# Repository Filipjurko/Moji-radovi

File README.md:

# Moji-radovi
Neki od mojih dosadašnjih radova.
Rađeni su iz razonode i zbog želje za učenjem programiranja u Arduino i C++ environmentu,
te cratnja u ad programima kao što su Fusion 360 i Solidworks.
Nekoliko od ovih projekata išlo je na natjecanja i svi su dobivali nagrade. 
Trenutno nemam ni jedan fizički izrađen projekt jer sam sve prototipe prodao ili ih poklonio.
KOntaktiram vas iz želje za učenjem ranog dizajna proizvoda i kako ga izbaciti na tržište kroz suradnju
s vašom kompanijom. Nadam se da ćete uvažiti moj upit. Hvala.

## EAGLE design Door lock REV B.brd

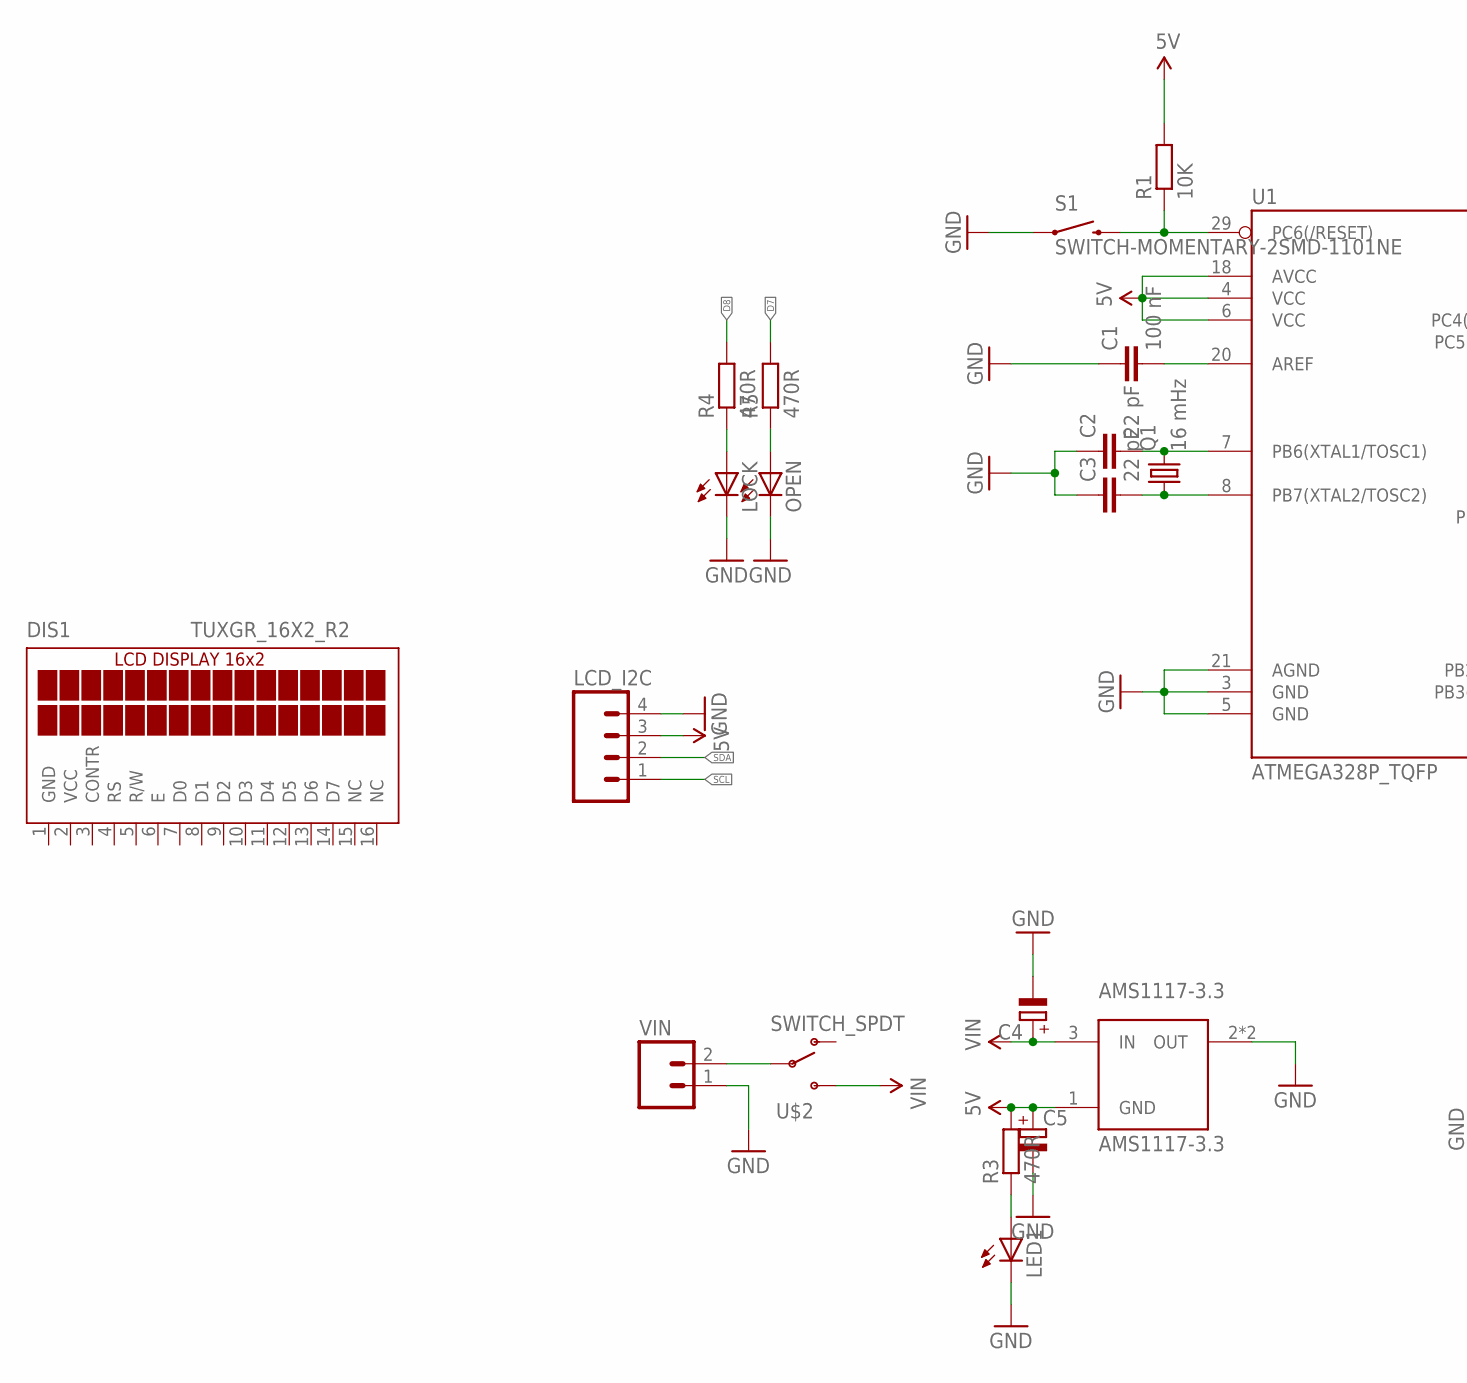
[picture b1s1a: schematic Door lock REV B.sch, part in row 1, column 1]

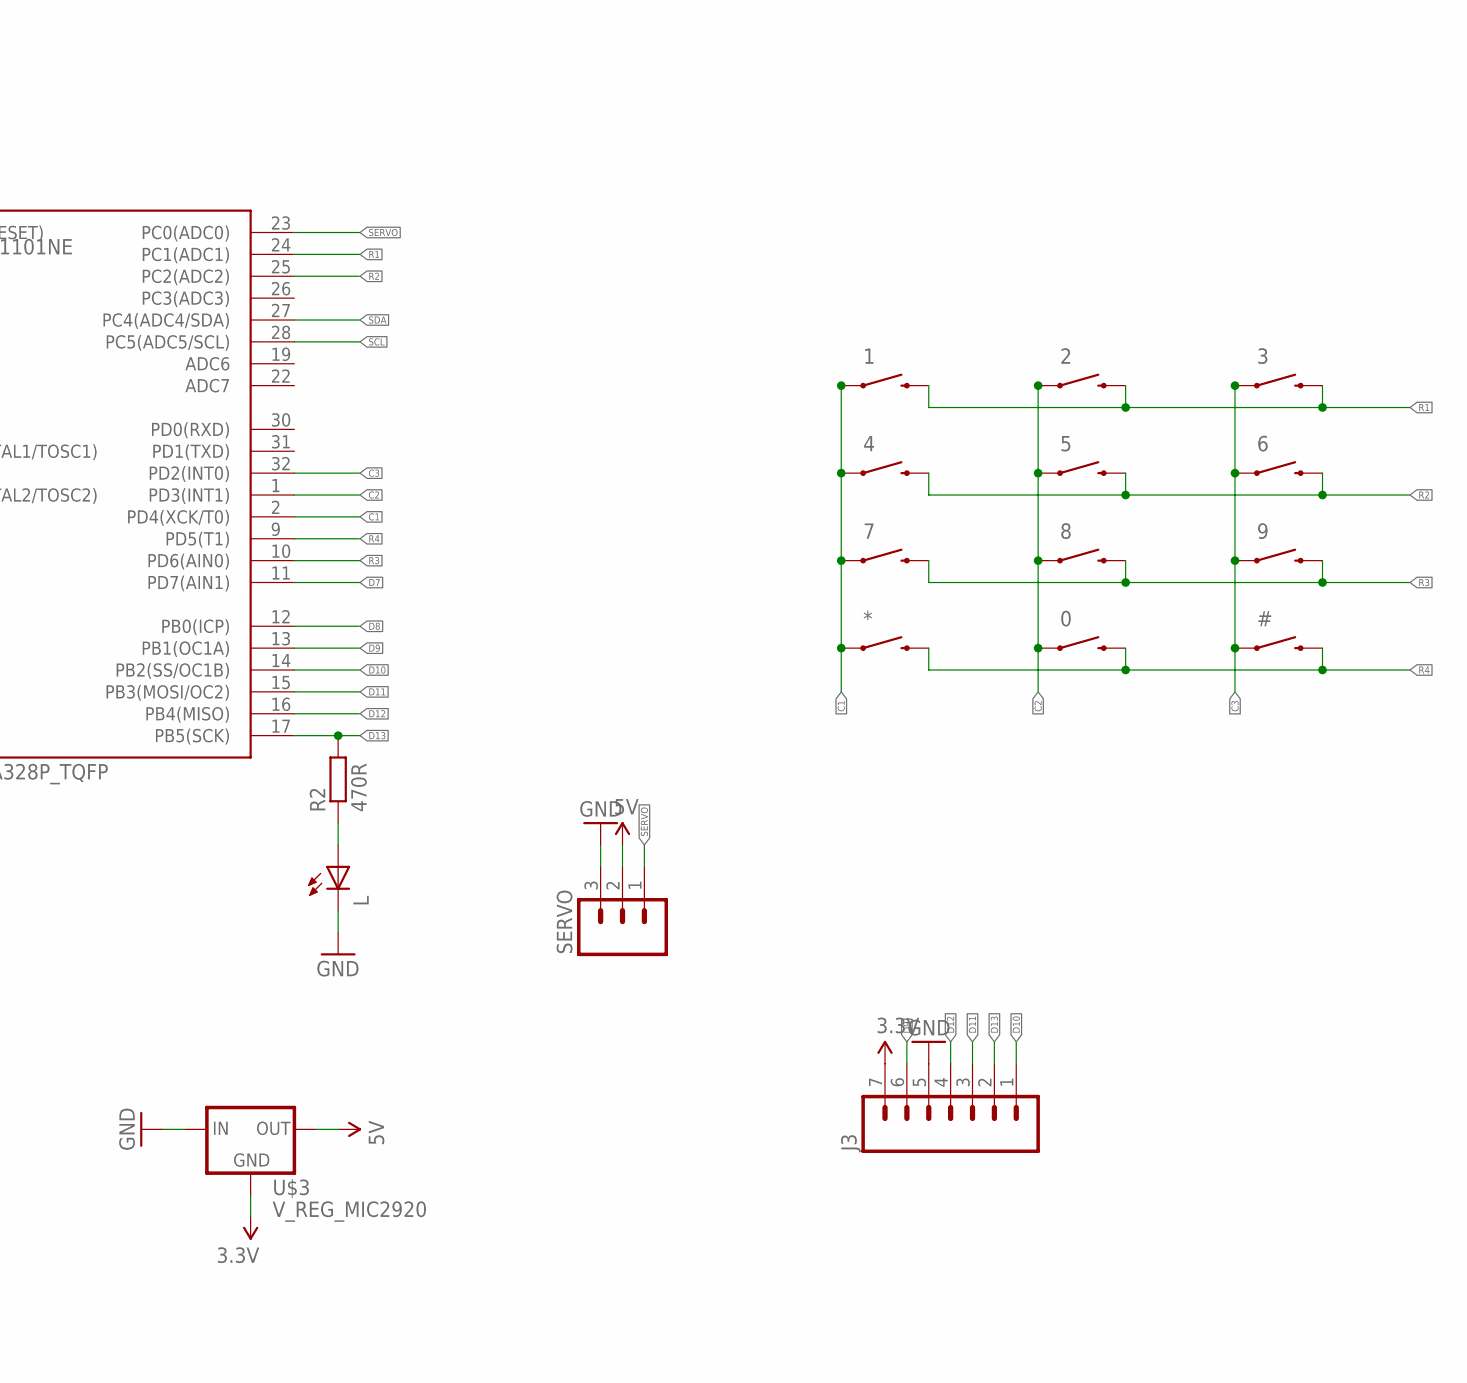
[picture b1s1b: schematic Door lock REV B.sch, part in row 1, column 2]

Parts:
0, 1, 2, 3, 4, 5, 6, 7, 8, 9: SWITCH-MOMENTARY-2PTH; TACTILE-PTH
#: SWITCH-MOMENTARY-2PTH; TACTILE-PTH
*: SWITCH-MOMENTARY-2PTH; TACTILE-PTH
AMS1117-3.3: AMS1117-3.3; SOT89
C1: 100 nF; C0603
C2, C3: 22 pF; C0603
C4, C5: CPOL-EUSMCA; SMC_A
DIS1: TUXGR_16X2_R2
J3: M07; 1X07
L: LEDCHIPLED_0805; CHIPLED_0805
LCD_I2C: M04PTH; 1X04
LED1: LEDCHIPLED_0805; CHIPLED_0805
LOCK: LED3MM
OPEN: LED3MM
Q1: 16 mHz; HC49/S
R1: 10K; R0603
R2, R3, R4, R5: 470R; R0603
S1: SWITCH-MOMENTARY-2SMD-1101NE; TACTILE-SWITCH-1101NE
SERVO: M03PTH; 1X03
U1: ATMEGA328P_TQFP; TQFP32-08
U$2: SWITCH_SPDT; KPS-1290
U$3: V_REG_MIC2920; SOT223
VIN: M02PTH3; 1X02_LONGPADS

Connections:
3.3V: J3.7, U$3.2 (GND)
5V: AMS1117-3.3.1 (GND), C5.+, LCD_I2C.3, R1.2, R3.2, SERVO.2, U1.4 (VCC), U1.6 (VCC), U1.18 (AVCC), U$3.3 (OUT)
C1: 1.1, 4.1, 7.1, *.1, U1.2 (PD4(XCK/T0))
C2: 0.1, 2.1, 5.1, 8.1, U1.1 (PD3(INT1))
C3: 3.1, 6.1, 9.1, #.1, U1.32 (PD2(INT0))
D7: R5.2, U1.11 (PD7(AIN1))
D8: R4.2, U1.12 (PB0(ICP))
D9: J3.6, U1.13 (PB1(OC1A))
D10: J3.1, U1.14 (PB2(SS/OC1B))
D11: J3.3, U1.15 (PB3(MOSI/OC2))
D12: J3.4, U1.16 (PB4(MISO))
D13: J3.2, R2.2, U1.17 (PB5(SCK))
GND: AMS1117-3.3.2 (OUT), AMS1117-3.3.2@1 (OUT), C1.1, C2.1, C3.1, C4.-, C5.-, DIS1.1 (GND), J3.5, L.C, LCD_I2C.4, LED1.C, LOCK.K (C), OPEN.K (C), S1.1, SERVO.3, U1.3 (GND), U1.5 (GND), U1.21 (AGND), U$3.1 (IN), VIN.1
unnamed: L.A, R2.1
unnamed: LOCK.A, R4.1
unnamed: C3.2, Q1.1, U1.8 (PB7(XTAL2/TOSC2))
unnamed: C2.2, Q1.2, U1.7 (PB6(XTAL1/TOSC1))
unnamed: OPEN.A, R5.1
unnamed: C1.2, U1.20 (AREF)
unnamed: R1.1, S1.2, U1.29 (PC6(/RESET))
unnamed: LED1.A, R3.1
unnamed: U$2.P, VIN.2
R1: 1.3 (2), 2.3 (2), 3.3 (2), U1.24 (PC1(ADC1))
R2: 4.3 (2), 5.3 (2), 6.3 (2), U1.25 (PC2(ADC2))
R3: 7.3 (2), 8.3 (2), 9.3 (2), U1.10 (PD6(AIN0))
R4: 0.3 (2), #.3 (2), *.3 (2), U1.9 (PD5(T1))
SCL: LCD_I2C.1, U1.28 (PC5(ADC5/SCL))
SDA: LCD_I2C.2, U1.27 (PC4(ADC4/SDA))
SERVO: SERVO.1, U1.23 (PC0(ADC0))
VCC: DIS1.2 (VCC)
VIN: AMS1117-3.3.3 (IN), C4.+, U$2.S

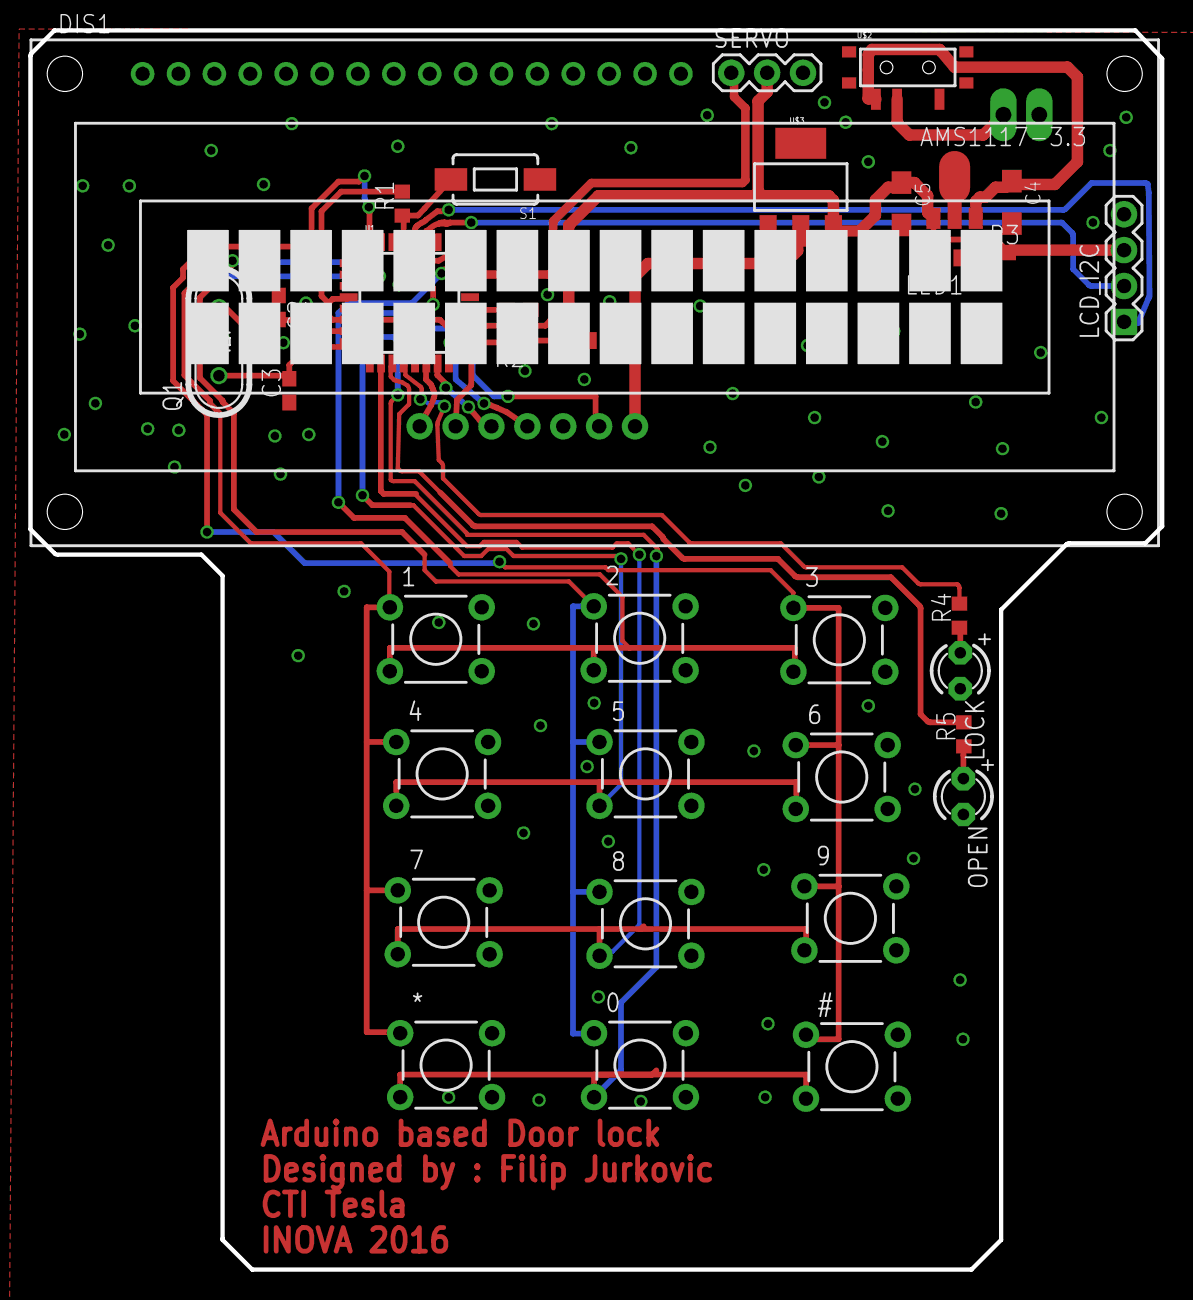
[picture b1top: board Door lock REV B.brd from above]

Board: 2 copper layers, 80.1 x 87.7 mm, 37 parts (1 on the bottom side), 30 nets.

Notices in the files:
parts and their libraries:
SparkFun-Electromechanical: Licensing: Creative Commons ShareAlike 4.0 International - https://creativecommons.org/licenses/by-sa/4.0
